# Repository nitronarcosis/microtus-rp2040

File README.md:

#  What
Microtus is a miniature joystick/button/rotary encoder board designed to approximate the functionality of a traditional mouse. The idea was to create a small, independent board that would communicate with a keyboard over I^2^C. I designed two versions, one based on the RP2040 that should be able to run KMK or QMK (eventually), the other as a minimum viable product based on the ATtiny85 which was abandoned when I realized how backwards the chip market is and the much less capable ATtiny cost more than the RP2040.
#### Parts

 - 5-way analog joystick --- for 2d pointer control
 - low-profile Kailh Choc switches --- dedicated buttons for left/right click
 - 90°? Rotary encoder --- for scrolling
 - USB type C 2.0 --- for programming or independent use
 - JST SH 4-pin connector --- for connecting via I^2^C (ala Qwiic)

# Why

I build a cool new keyboard and wanted to see if I could design a "mouse" that was complementary.
#### Name
It's not a mouse but it's a genus of small-eared voles. It's related enough but not the same.

# Renders

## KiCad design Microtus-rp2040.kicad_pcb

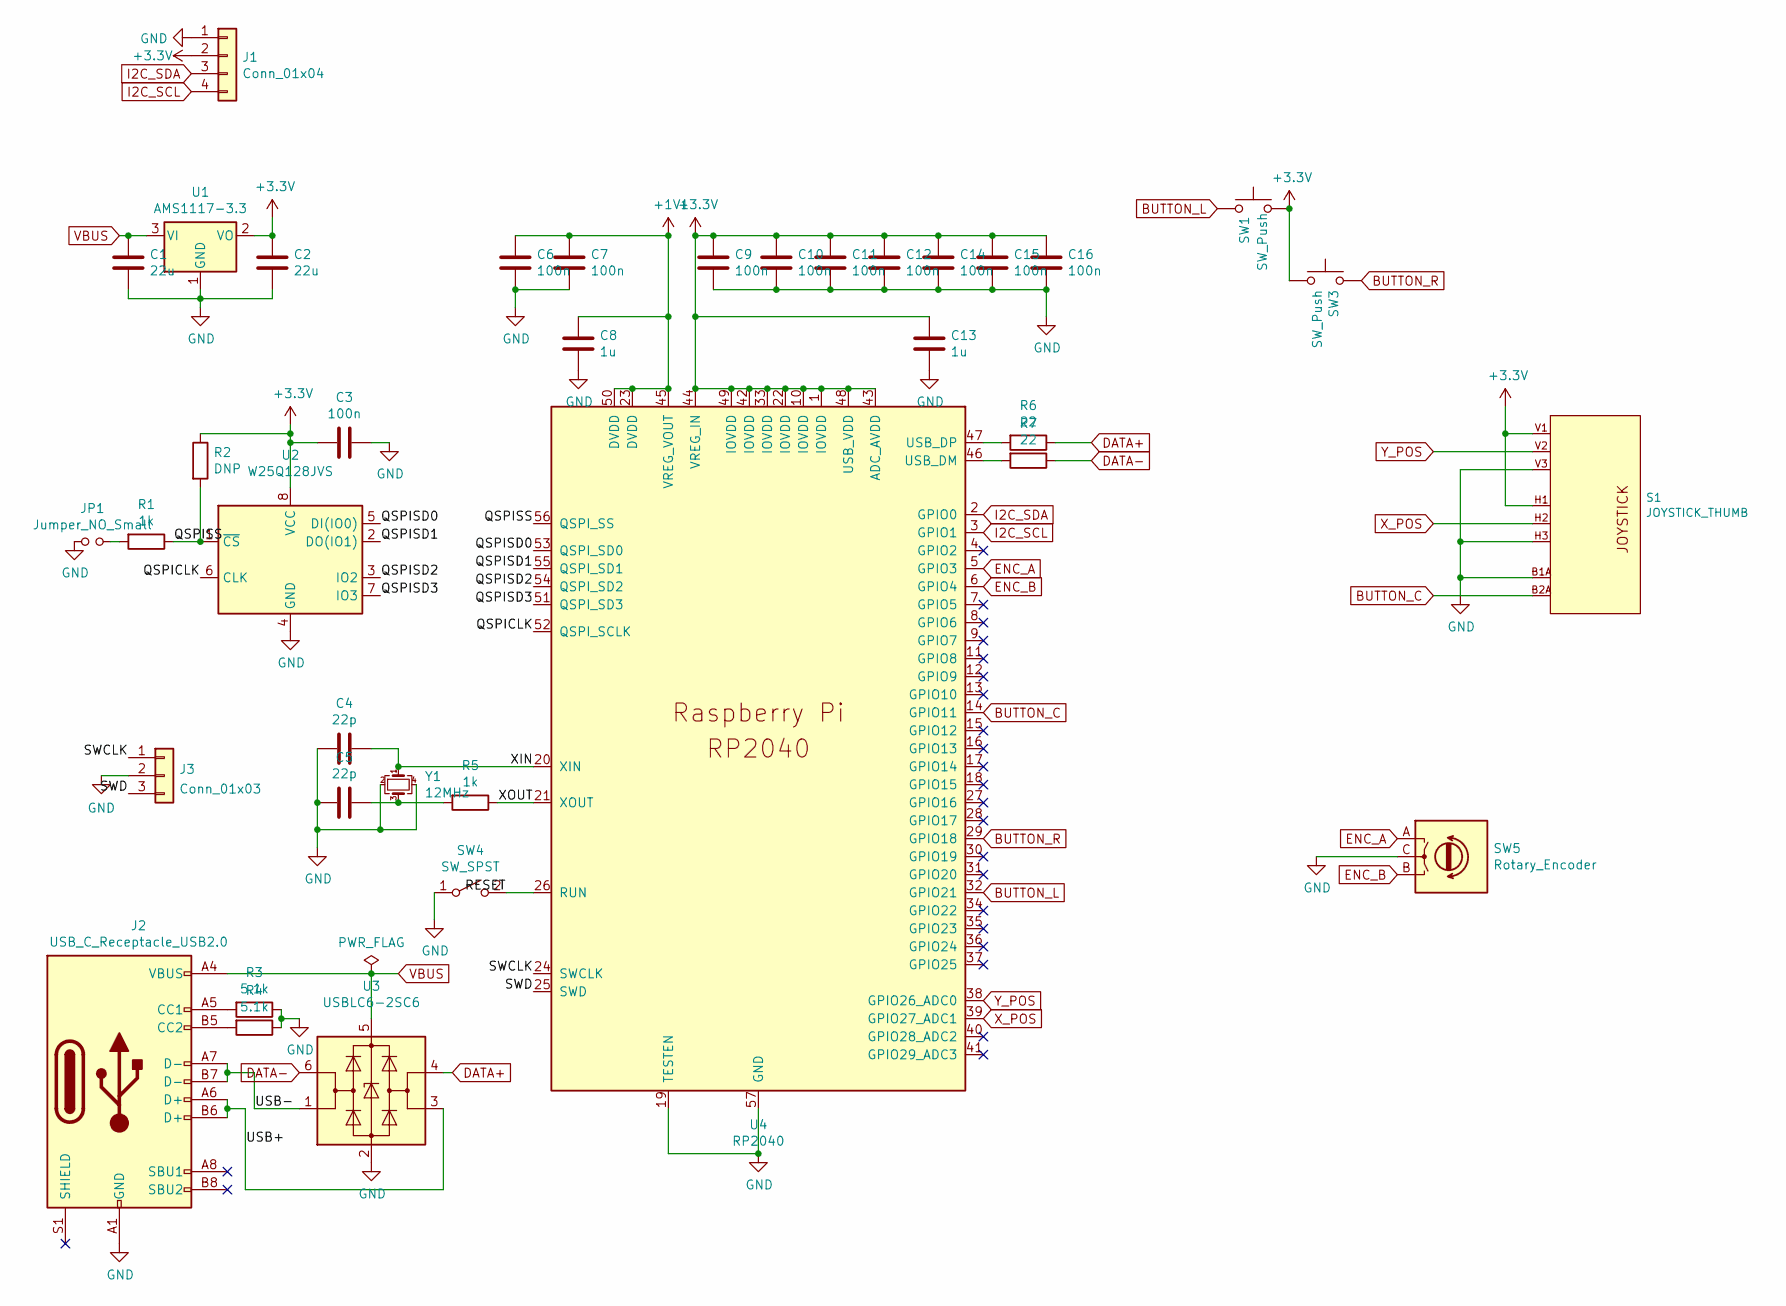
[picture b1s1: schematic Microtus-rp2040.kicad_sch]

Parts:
C1, C2: 22u; C_0603_1608Metric; LCSC C59461
C3, C6, C7, C9, C10, C11, C12, C14, C15, C16: 100n; C_0402_1005Metric; LCSC C1525
C4, C5: 22p; C_0402_1005Metric; LCSC C1555
C8, C13: 1u; C_0402_1005Metric; LCSC C52923
J1: Conn_01x04; JST_SH_SM04B-SRSS-TB_1x04-1MP_P1.00mm_Horizontal
J2: USB_C_Receptacle_USB2.0; USB_C_Receptacle_HRO_TYPE-C-31-M-12
J3: Conn_01x03; PinHeader_1x03_P2.54mm_Vertical
JP1: Jumper_NO_Small; PinHeader_1x02_P2.00mm_Vertical
R1, R5: 1k; R_0402_1005Metric; LCSC C11702
R2: DNP; R_0402_1005Metric
R3, R4: 5.1k; R_0402_1005Metric; LCSC C25905
R6, R7: 22; R_0402_1005Metric; LCSC C25092
S1: JOYSTICK_THUMB; JOYSTICK
SW1, SW3: SW_Push; Kailh-PG1350-1u-NoLED
SW4: SW_SPST; SW_SPST_EVQP0; LCSC C713479
SW5: Rotary_Encoder; RotaryEncoder_Alps_EC11E_Vertical_H20mm
U1: AMS1117-3.3; SOT-223-3_TabPin2; LCSC C6186
U2: W25Q128JVS; SOIC-8_5.23x5.23mm_P1.27mm; LCSC C97521
U3: USBLC6-2SC6; SOT-23-6; LCSC C2827654
U4: RP2040; RP2040-QFN-56; LCSC C2040
Y1: 12MHz; Crystal_SMD_3225-4Pin_3.2x2.5mm; LCSC C9002

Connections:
+1V1: C6.1, C7.1, C8.1, U4.23 (DVDD), U4.45 (VREG_VOUT), U4.50 (DVDD)
+3V3: C2.1, C3.2, C9.1, C10.1, C11.1, C12.1, C13.1, C14.1, C15.1, C16.1, J1.2, R2.1, S1.H1 (H+), S1.V1 (V+), SW1.2, SW3.1, U1.2 (VO), U2.8 (VCC), U4.1 (IOVDD), U4.10 (IOVDD), U4.22 (IOVDD), U4.33 (IOVDD), U4.42 (IOVDD), U4.43 (ADC_AVDD), U4.44 (VREG_IN), U4.48 (USB_VDD), U4.49 (IOVDD)
/QSPICLK: U2.6 (CLK), U4.52 (QSPI_SCLK)
/QSPISD0: U2.5 (DI(IO0)), U4.53 (QSPI_SD0)
/QSPISD1: U2.2 (DO(IO1)), U4.55 (QSPI_SD1)
/QSPISD2: U2.3 (IO2), U4.54 (QSPI_SD2)
/QSPISD3: U2.7 (IO3), U4.51 (QSPI_SD3)
/QSPISS: R1.1, R2.2, U2.1 (~CS), U4.56 (QSPI_SS)
/RESET: SW4.2 (B), U4.26 (RUN)
/SWCLK: J3.1, U4.24 (SWCLK)
/SWD: J3.3, U4.25 (SWD)
/USB+: J2.A6 (D+), J2.B6 (D+), U3.3 (I/O2)
/USB-: J2.A7 (D-), J2.B7 (D-), U3.1 (I/O1)
/XIN: C4.1, U4.20 (XIN), Y1.1
/XOUT: R5.1, U4.21 (XOUT)
BUTTON_L: SW1.1, U4.32 (GPIO21)
BUTTON_R: SW3.2, U4.29 (GPIO18)
DATA+: R6.1, U3.4 (I/O2)
DATA-: R7.1, U3.6 (I/O1)
ENC_A: SW5.A, U4.5 (GPIO3)
ENC_B: SW5.B, U4.6 (GPIO4)
I2C_SCL: J1.4, U4.3 (GPIO1)
I2C_SDA: J1.3, U4.2 (GPIO0)
unnamed: C5.1, R5.2, Y1.3
unnamed: J2.A5 (CC1), R3.2
unnamed: J2.B5 (CC2), R4.2
unnamed: JP1.2, R1.2
unnamed: R6.2, U4.47 (USB_DP)
unnamed: R7.2, U4.46 (USB_DM)
VBUS: C1.1, J2.A4 (VBUS), J2.A9 (VBUS), J2.B4 (VBUS), J2.B9 (VBUS), U1.3 (VI), U3.5 (VBUS)
X_POS: S1.H2 (H), U4.39 (GPIO27_ADC1)
Y_POS: S1.V2 (V), U4.38 (GPIO26_ADC0)

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
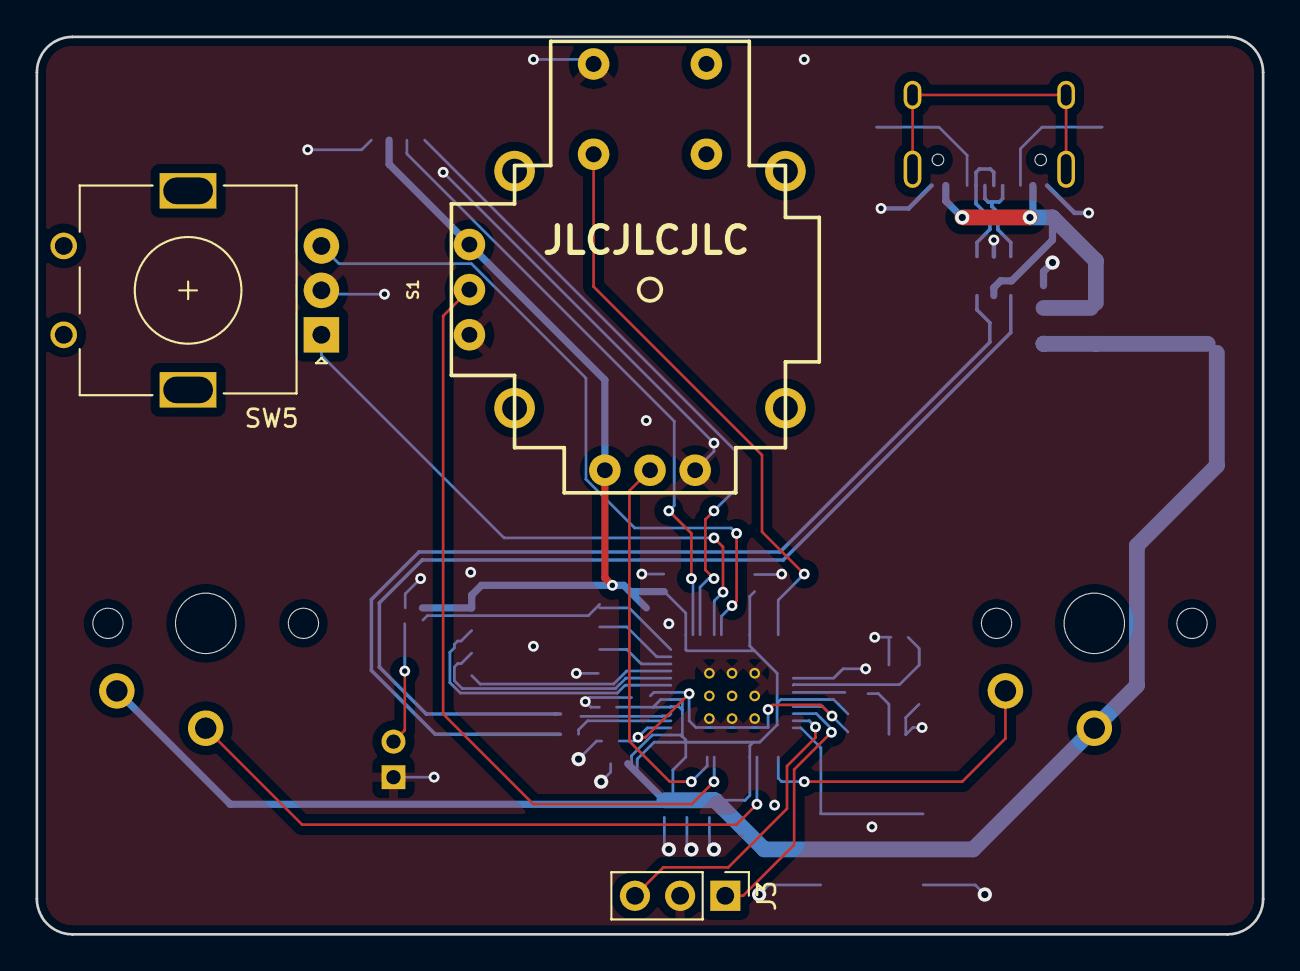
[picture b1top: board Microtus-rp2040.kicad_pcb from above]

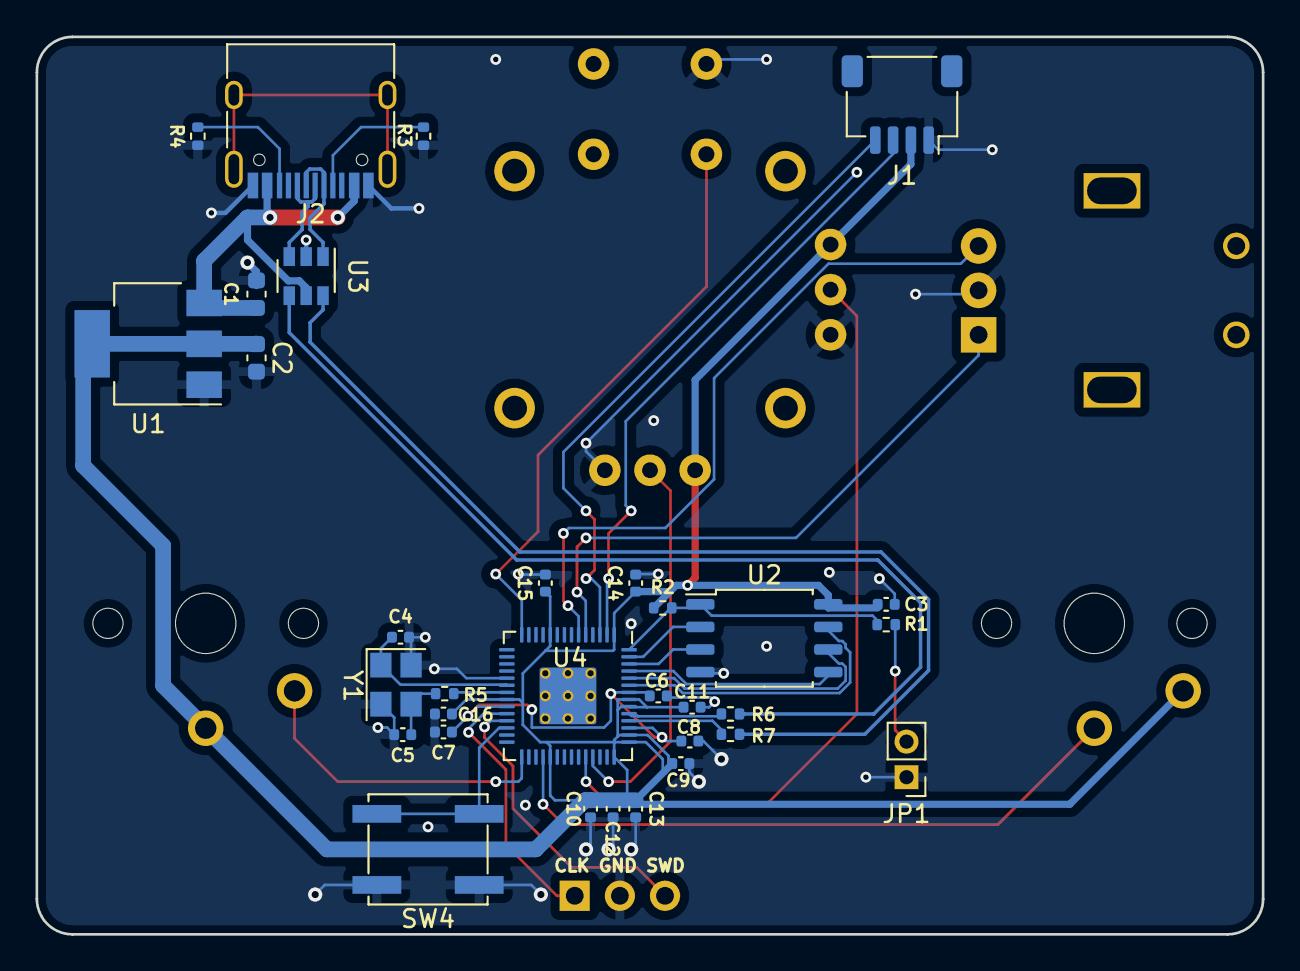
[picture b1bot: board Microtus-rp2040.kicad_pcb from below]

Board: 2 copper layers, 69.0 x 50.5 mm, 37 parts (32 on the bottom side), 34 nets.

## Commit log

2021-12-26 moving things around
2021-12-27 add SWD and switch to KiCad 6
2021-12-27 Generate production files
2022-07-17 Add license
2022-07-25 Adding pictures, and a README!!
2022-07-25 Update README.md
    Adding renders to README
